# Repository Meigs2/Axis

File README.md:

# Axis

This project is unfinished and is under active development.

For updates, come join the discord: https://discord.gg/SSdEUZB4Xh

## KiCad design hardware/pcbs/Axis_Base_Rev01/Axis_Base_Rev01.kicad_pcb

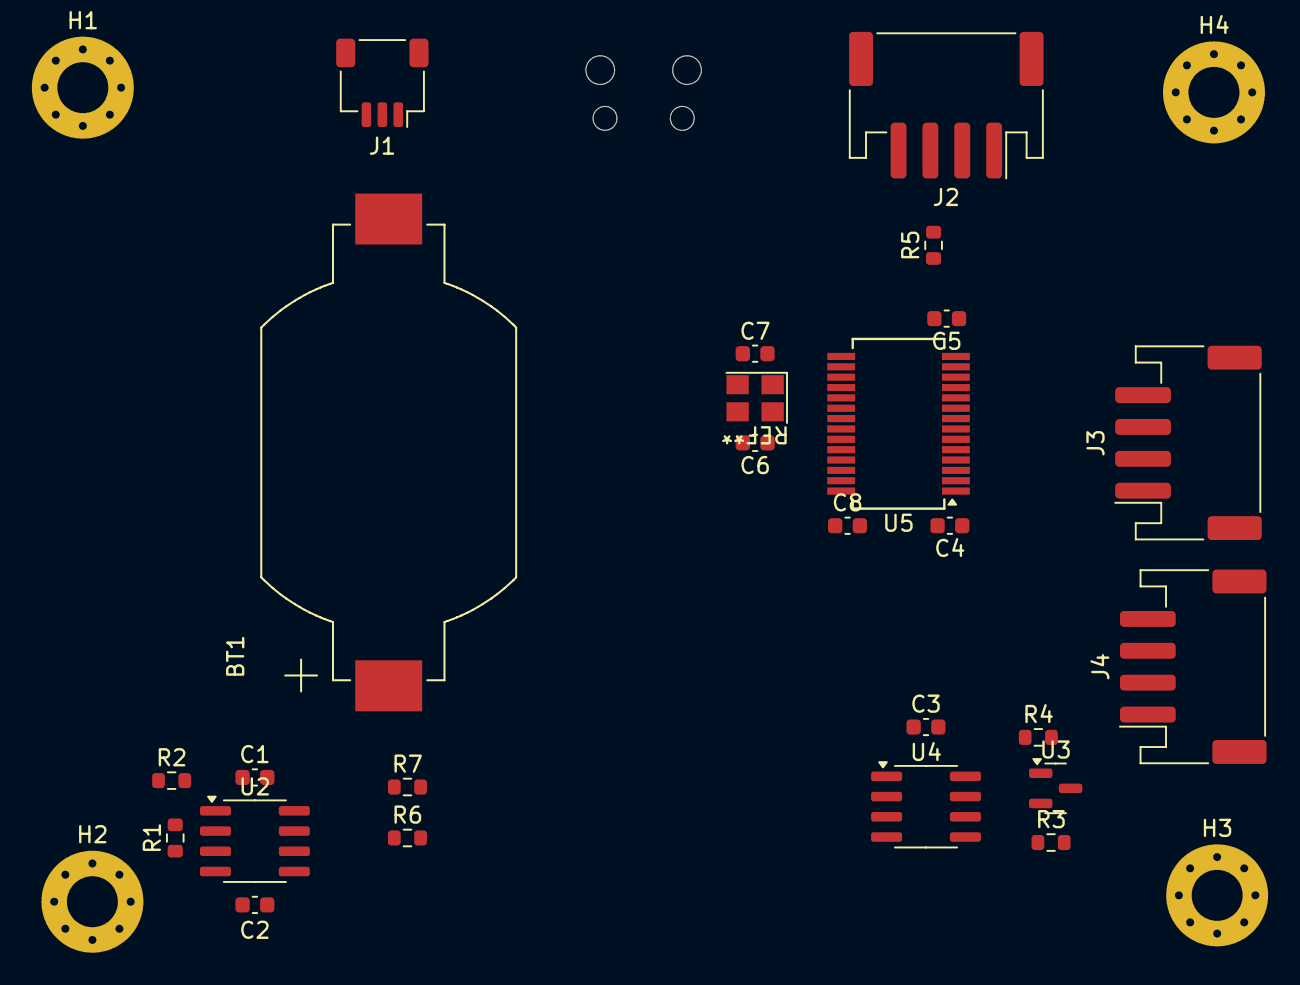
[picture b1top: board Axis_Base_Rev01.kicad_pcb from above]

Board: 4 copper layers, 30 parts (1 on the bottom side), 28 nets, no tracks yet.

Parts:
BT1: BA2032; BAT_BU2032SM-BT-GTR
C1, C2, C3, C4, C5, C8: 0.1u; C_0603_1608Metric
C6, C7: 26p; C_0603_1608Metric
H1, H2, H3, H4: MountingHole; MountingHole_3.2mm_M3_Pad_Via
J1: SWD; JST_SH_SM03B-SRSS-TB_1x03-1MP_P1.00mm_Horizontal
J2: CAN_1; JST_PH_S4B-PH-SM4-TB_1x04-1MP_P2.00mm_Horizontal
J3: CAN_2; JST_PH_S4B-PH-SM4-TB_1x04-1MP_P2.00mm_Horizontal
J4: CAN_3; JST_PH_S4B-PH-SM4-TB_1x04-1MP_P2.00mm_Horizontal
R1, R2, R3, R4, R5, R6, R7: 1k; R_0603_1608Metric
U1: Pico; RPi_Pico_SMD_No_Silkscreen
U2: DS3231MZ; SOIC-8_3.9x4.9mm_P1.27mm
U3: DS2411R; SOT-23
U4: FM24CL16B; SOIC-8_3.9x4.9mm_P1.27mm
U5: MCP251863T-H; SSOP-28_5.3x10.2mm_P0.65mm
Y1: ABM8G-20.000MHZ-18-D2Y-T; Oscillator_Crystal_Abracon_SMD_ABM8G

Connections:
+3V3: C1.1, C3.1, C4.1, C5.1, R1.1, R2.1, R3.1, R6.1, R7.1, U1.36 (3V3_OUT), U2.2 (VCC), U3.2 (VIN), U4.8 (VDD), U5.1 (VIO), U5.14 (VDD)
+5V: C8.1, J2.1, J3.1, J4.1, U1.40 (VBUS), U5.25 (VCC)
+BATT: BT1.1 (+), C2.1, U2.6 (VBAT)
/1WIRE: R4.2, U1.26 (GPIO20)
/CANH: J2.2, J3.2, J4.2, R5.1, U5.4 (CANH)
/CANL: J2.3, J3.3, J4.3, R5.2, U5.3 (CANL)
/I2C0_SCL: R7.2, U1.22 (GPIO17), U2.8 (SCL), U4.6 (SCL)
/I2C0_SDA: R6.2, U1.21 (GPIO16), U2.7 (SDA), U4.5 (SDA)
/RTC_CLK: R1.2, U1.24 (GPIO18), U2.1 (32KHZ)
/SPI0_MISO: U1.1 (GPIO0), U5.11 (SDO)
/SPI0_MOSI: U1.5 (GPIO3), U5.10 (SDI)
/SPI0_SCK: U1.4 (GPIO2), U5.9 (SCK)
/STBY: U1.10 (GPIO7), U5.5 (STBY)
/SWCLK: J1.1, U1.41 (SWCLK)
/SWDIO: J1.3, U1.43 (SWDIO)
/~SPI0_CS: U1.2 (GPIO1), U5.13 (~CS)
/~TIMER_INT: R2.2, U1.25 (GPIO19), U2.3 (~INT/SQW)
/~nINT1: U1.7 (GPIO5), U5.6 (~nINT1)
/~nINT2: U1.9 (GPIO6), U5.7 (~nINT2)
/~nINT: U1.6 (GPIO4), U5.19 (~nINT)
GND: BT1.2 (-), C1.2, C2.2, C3.2, C4.2, C5.2, C8.2, J1.2, J2.4, J3.4, J4.4, U1.3 (GND), U1.8 (GND), U1.13 (GND), U1.18 (GND), U1.23 (GND), U1.28 (GND), U1.38 (GND), U1.42 (GND), U2.5 (GND), U3.3 (GND), U4.4 (VSS), U4.7 (WP), U5.22 (VSS), U5.24 (GND), Y1.1, Y1.3
unnamed: C6.2, Y1.4
unnamed: C7.2, Y1.2
unnamed: R3.2, R4.1, U3.1 (I/O)
unnamed: C7.1, U5.21 (OSC1)
unnamed: C6.1, U5.20 (OSC2)
unnamed: U5.16 (RxCAN), U5.28 (RXD)
unnamed: U5.15 (TxCAN), U5.23 (TXD)

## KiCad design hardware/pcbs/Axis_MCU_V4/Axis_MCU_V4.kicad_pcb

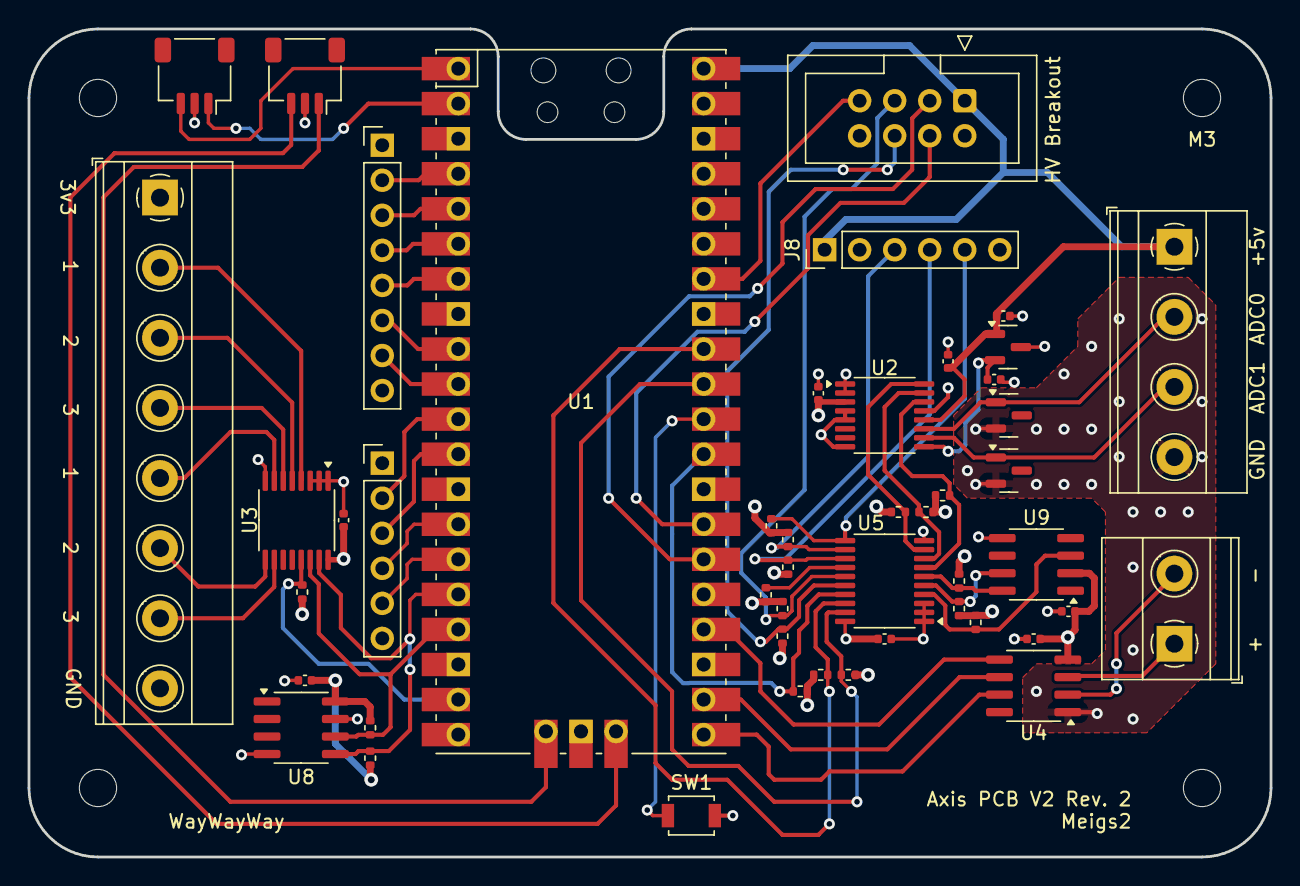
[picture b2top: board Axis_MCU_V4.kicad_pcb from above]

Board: 4 copper layers, 90.0 x 60.0 mm, 51 parts (0 on the bottom side), 53 nets.

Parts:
C1, C2, C3, C4, C5, C7, C8, C9, C10: 0.1u; C_0402_1005Metric
D1, D2: 4.7v; SOT-23
H1, H2, H3, H4: MountingHole; MountingHole_2.7mm_M2.5
J1: SWD; JST_SH_SM03B-SRSS-TB_1x03-1MP_P1.00mm_Horizontal
J2: GPIO; TerminalBlock_Phoenix_MKDS-1,5-8-5.08_1x08_P5.08mm_Horizont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
J3: Conn_01x04; TerminalBlock_Phoenix_MKDS-1,5-4-5.08_1x04_P5.08mm_Horizont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
J4: UART; JST_SH_SM03B-SRSS-TB_1x03-1MP_P1.00mm_Horizontal
J5: Conn_01x02; TerminalBlock_Phoenix_MKDS-1,5-2-5.08_1x02_P5.08mm_Horizont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
J7: EXT_SPI; PinHeader_1x06_P2.54mm_Vertical
J8: EXT_I2C; PinHeader_1x06_P2.54mm_Vertical
J9: GPIO; PinHeader_1x08_P2.54mm_Vertical
J10: HV_IDC; IDC-Header_2x04_P2.54mm_Vertical
R1, R2, R3, R4, R5, R6, R7, R8, R9, R10, R11, R12, R13, R14, R15, R16, R17, R18: 1k; R_0402_1005Metric
SW1: RES; SW_SPST_B3U-1000P
U1: Pico; RPi_Pico_SMD_TH_No_Silkscreen
U2: ADS1119IPWR; TSSOP-16_4.4x5mm_P0.65mm
U3: TCA9534; TSSOP-16_4.4x5mm_P0.65mm
U4: MAX31855EASA; SOIC-8_3.9x4.9mm_P1.27mm
U5: PCA9544APWR; TSSOP-20_4.4x6.5mm_P0.65mm
U7: MAX6107; SOT-23
U8: FM24CL16B; SOIC-8_3.9x4.9mm_P1.27mm
U9: DS3231MZ; SOIC-8_3.9x4.9mm_P1.27mm

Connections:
+3V3: C1.1, C3.1, C4.1, C5.1, C7.1, C10.1, J2.1, J7.1, J8.2, J9.1, J10.2, R1.1, R2.1, R3.1, R4.1, R5.1, R6.1, R7.1, R8.1, R9.1, R10.1, R11.1, R12.1, R13.1, R14.1, R15.1, R16.1, R17.1, R18.1, U1.36 (3V3_OUT), U2.3 (~RESET), U2.13 (DVDD), U3.16 (VDD), U4.4 (V_CC), U5.20 (VDD), U8.8 (VDD), U9.2 (VCC)
+5V: C2.1, C8.1, J3.1, J8.1, J10.1, U1.40 (VBUS), U2.12 (AVDD), U7.1 (IN)
/4.5V_VREF: C9.1, U2.9 (REFP), U7.2 (OUT)
/ADC_0: D1.1 (K), J3.2, U2.11 (AIN0)
/ADC_1: D2.1 (K), J3.3, U2.10 (AIN1)
/ADS_SCL: R8.2, U2.16 (SCL), U5.9 (SC1)
/ADS_SDA: R7.2, U2.15 (SDA), U5.8 (SD1)
/EXT_SCL: J8.4, R17.2, U5.13 (SC2)
/EXT_SDA: J8.3, R16.2, U5.12 (SD2)
/GPIO2: J9.2, U1.4 (GPIO2)
/GPIO3: J9.3, U1.5 (GPIO3)
/GPIO4: J9.4, U1.6 (GPIO4)
/GPIO5: J9.5, U1.7 (GPIO5)
/GPIO6: J9.6, U1.9 (GPIO6)
/GPIO7: J9.7, U1.10 (GPIO7)
/HV_IO1: J10.3, U1.26 (GPIO20)
/HV_IO2: J10.7, U1.34 (GPIO28_ADC2)
/HV_SCL: J10.6, R14.2, U5.16 (SC3)
/HV_SDA: J10.5, R13.2, U5.15 (SD3)
/I2C0_SCL: R2.2, U1.17 (GPIO13), U3.14 (SCL), U8.6 (SCL)
/I2C0_SDA: R1.2, U1.16 (GPIO12), U3.15 (SDA), U8.5 (SDA)
/I2C1_SCL: R4.2, U1.32 (GPIO27_ADC1), U5.18 (SCL)
/I2C1_SDA: R5.2, U1.31 (GPIO26_ADC0), U5.19 (SDA)
/IO_1: J2.2, U3.4 (P0)
/IO_2: J2.3, U3.5 (P1)
/IO_3: J2.4, U3.6 (P2)
/IO_4: J2.5, U3.7 (P3)
/IO_5: J2.6, U3.9 (P4)
/IO_6: J2.7, U3.10 (P5)
/SPI0_RX: U1.21 (GPIO16), U4.7 (SO)
/SPI0_SCK: U1.24 (GPIO18), U4.5 (SCK)
/SPI1_RX: J7.2, U1.11 (GPIO8)
/SPI1_SCK: J7.4, U1.14 (GPIO10)
/SPI1_TX: J7.5, U1.15 (GPIO11)
/SWCLK: J1.1, U1.41 (SWCLK)
/SWDIO: J1.3, U1.43 (SWDIO)
/THCPL1_NEG: J5.2, U4.2 (T-)
/THCPL1_POS: J5.1, U4.3 (T+)
/TIMER_SCL: R11.2, U5.6 (SC0), U9.8 (SCL)
/TIMER_SDA: R10.2, U5.5 (SD0), U9.7 (SDA)
/UART_RX: J4.1, U1.2 (GPIO1)
/UART_TX: J4.3, U1.1 (GPIO0)
/ZC_SIG: J10.4, U1.27 (GPIO21)
/~ADS_RDY: R9.2, U2.14 (~DRDY), U5.7 (~INT1)
/~EXT_INT: J8.5, R18.2, U5.11 (~INT2)
/~INT_3: R15.2, U5.14 (~INT3)
/~IO_INT: R3.2, U1.19 (GPIO14), U3.13 (~INT)
/~MUX_INT: R6.2, U1.29 (GPIO22), U5.17 (~INT)
/~SPI0_CS0: U1.22 (GPIO17), U4.6 (~CS)
/~SPI1_CS0: J7.3, U1.12 (GPIO9)
/~TIMER_INT: R12.2, U5.4 (~INT0), U9.3 (~INT/SQW)
GND: C1.2, C2.2, C3.2, C4.2, C5.2, C7.2, C8.2, C9.2, C10.2, D1.2 (A), D2.2 (A), J1.2, J2.8, J3.4, J4.2, J7.6, J8.6, J9.8, J10.8, SW1.1, U1.3 (GND), U1.8 (GND), U1.13 (GND), U1.18 (GND), U1.23 (GND), U1.28 (GND), U1.38 (GND), U1.42 (GND), U2.1 (A0), U2.2 (A1), U2.4 (DGND), U2.5 (AGND), U2.8 (REFN), U3.1 (A0), U3.2 (A1), U3.3 (A2), U3.8 (GND), U4.1 (GND), U5.1 (A0), U5.2 (A1), U5.3 (A2), U5.10 (VSS), U7.3 (GND), U8.4 (VSS), U8.7 (WP), U9.5 (GND)
unnamed: SW1.2, U1.30 (RUN)

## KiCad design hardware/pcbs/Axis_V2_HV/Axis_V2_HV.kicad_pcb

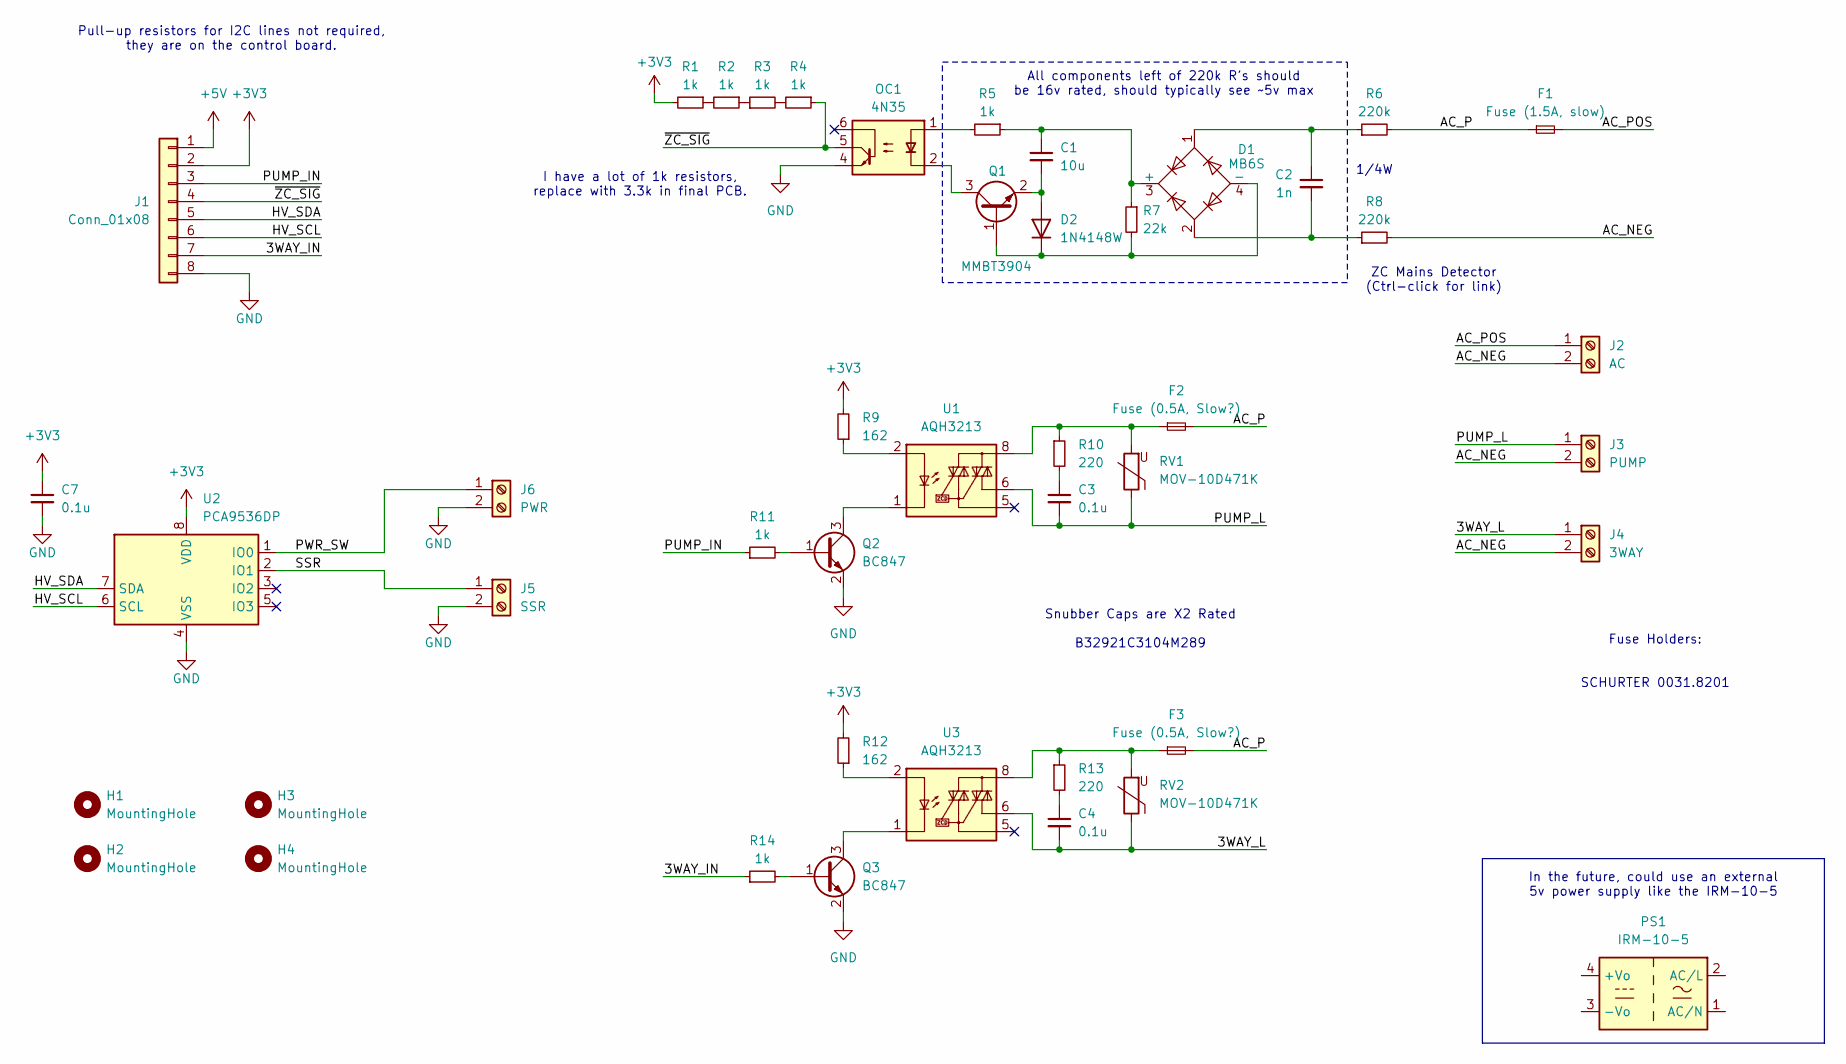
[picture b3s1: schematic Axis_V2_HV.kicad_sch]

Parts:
C1: 10u; C_1206_3216Metric
C2: 1n; C_1206_3216Metric
C3, C4: 0.1u; C_Rect_L13.0mm_W6.0mm_P10.00mm_FKS3_FKP3_MKS4
C7: 0.1u; C_0402_1005Metric
D1: MB6S; TO-269AA
D2: 1N4148W; D_SOD-123
F1: Fuse (1.5A, slow); Fuseholder_Cylinder-5x20mm_Schurter_0031_8201_Horizontal_Op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
F2, F3: Fuse (0.5A, Slow?); Fuseholder_Cylinder-5x20mm_Schurter_0031_8201_Horizontal_Op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
H1, H2, H3, H4: MountingHole; MountingHole_2.7mm_M2.5
J1: Conn_01x08; IDC-Header_2x04_P2.54mm_Vertical
J2: AC; TerminalBlock_Phoenix_MKDS-1,5-2-5.08_1x02_P5.08mm_Horizont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
J3: PUMP; TerminalBlock_Phoenix_MKDS-1,5-2-5.08_1x02_P5.08mm_Horizont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
J4: 3WAY; TerminalBlock_Phoenix_MKDS-1,5-2-5.08_1x02_P5.08mm_Horizont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
J5: SSR; TerminalBlock_Phoenix_MKDS-1,5-2-5.08_1x02_P5.08mm_Horizont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
J6: PWR; TerminalBlock_Phoenix_MKDS-1,5-2-5.08_1x02_P5.08mm_Horizont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
OC1: 4N35; SMDIP-6_W7.62mm
PS1: IRM-10-5; Converter_ACDC_MeanWell_IRM-10-xx_THT
Q1: MMBT3904; SOT-23
Q2, Q3: BC847; SOT-23
R1, R2, R3, R4, R11, R14: 1k; R_0402_1005Metric
R5: 1k; R_1206_3216Metric
R6, R8: 220k; R_Axial_DIN0207_L6.3mm_D2.5mm_P10.16mm_Horizontal
R7: 22k; R_1206_3216Metric
R9, R12: 162; R_0603_1608Metric
R10, R13: 220; R_Axial_DIN0207_L6.3mm_D2.5mm_P10.16mm_Horizontal
RV1, RV2: MOV-10D471K; RV_Disc_D12mm_W7.5mm_P7.5mm
U1, U3: AQH3213; DIP-8-N7_W7.62mm
U2: PCA9536DP; TSSOP-8_3x3mm_P0.65mm

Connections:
+3V3: C7.1, J1.2, R1.2, R9.2, R12.2, U2.8 (VDD)
+5V: J1.1
/3WAY_IN: J1.7, R14.1
/3WAY_L: C4.2, J4.1, RV2.1, U3.6
/AC_NEG: J2.2, J3.2, J4.2, R8.2
/AC_P: F1.1, F2.2, F3.2, R6.2
/AC_POS: F1.2, J2.1
/HV_SCL: J1.6, U2.6 (SCL)
/HV_SDA: J1.5, U2.7 (SDA)
/PUMP_IN: J1.3, R11.1
/PUMP_L: C3.2, J3.1, RV1.1, U1.6
/PWR_SW: J6.1, U2.1 (IO0)
/SSR: J5.1, U2.2 (IO1)
/~ZC_SIG: J1.4, OC1.5, R4.1
GND: C7.2, J1.8, J5.2, J6.2, OC1.4, Q2.2 (E), Q3.2 (E), U2.4 (VSS)
unnamed: C2.1, D1.1, R6.1
unnamed: C2.2, D1.2, R8.1
unnamed: C3.1, R10.2
unnamed: C4.1, R13.2
unnamed: C1.1, D1.3 (+), R5.1, R7.1
unnamed: D1.4 (-), D2.1 (K), Q1.1 (B), R7.2
unnamed: C1.2, D2.2 (A), Q1.2 (E)
unnamed: F2.1, R10.1, RV1.2, U1.8
unnamed: F3.1, R13.1, RV2.2, U3.8
unnamed: OC1.1, R5.2
unnamed: OC1.2, Q1.3 (C)
unnamed: Q2.1 (B), R11.2
unnamed: Q2.3 (C), U1.1, U1.3, U1.4
unnamed: Q3.1 (B), R14.2
unnamed: Q3.3 (C), U3.1, U3.3, U3.4
unnamed: R1.1, R2.2
unnamed: R2.1, R3.1
unnamed: R3.2, R4.2
unnamed: R9.1, U1.2
unnamed: R12.1, U3.2

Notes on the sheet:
Pull-up resistors for I2C lines not required, they are on the control board.
I have a lot of 1k resistors, replace with 3.3k in final PCB.
ZC Mains Detector (Ctrl-click for link)
1/4W
In the future, could use an external 5v power supply like the IRM-10-5
All components left of 220k R's should be 16v rated, should typically see ~5v max
Fuse Holders: SCHURTER 0031.8201
Snubber Caps are X2 Rated B32921C3104M289

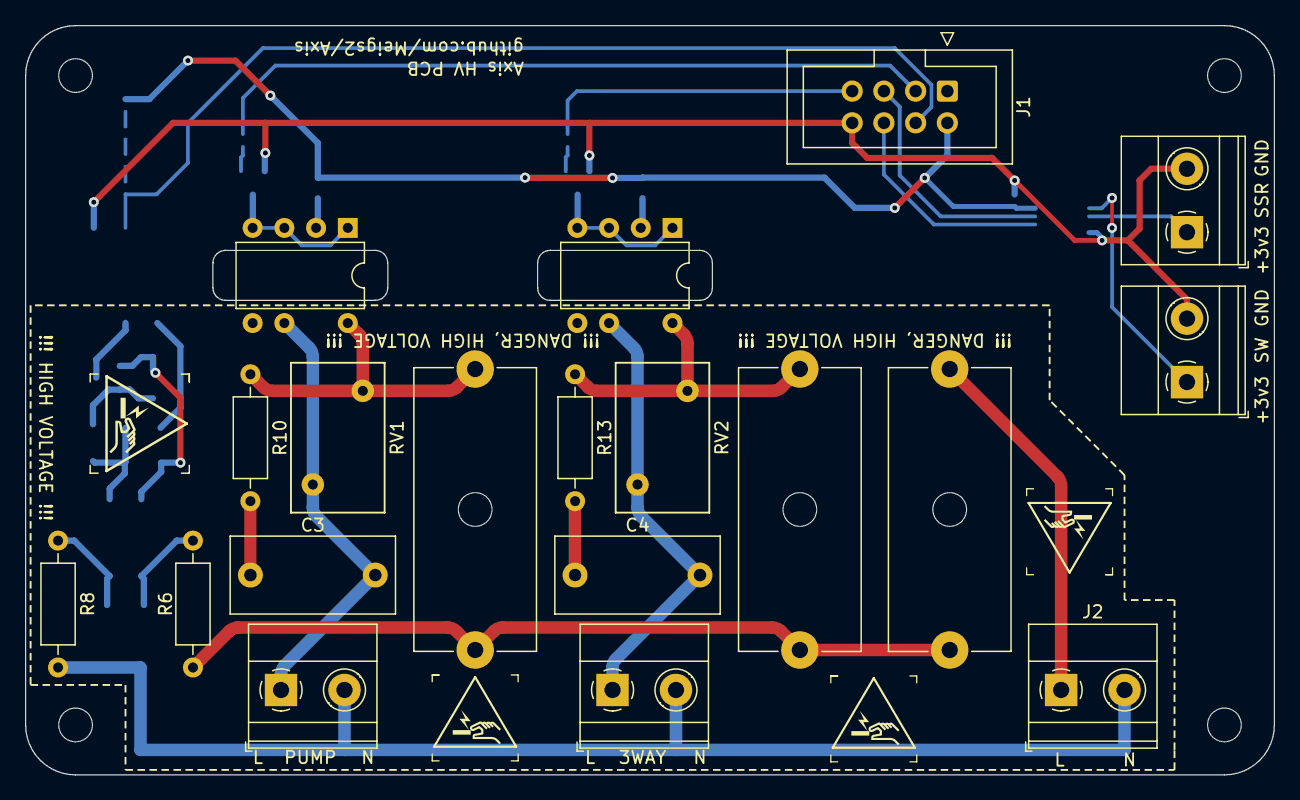
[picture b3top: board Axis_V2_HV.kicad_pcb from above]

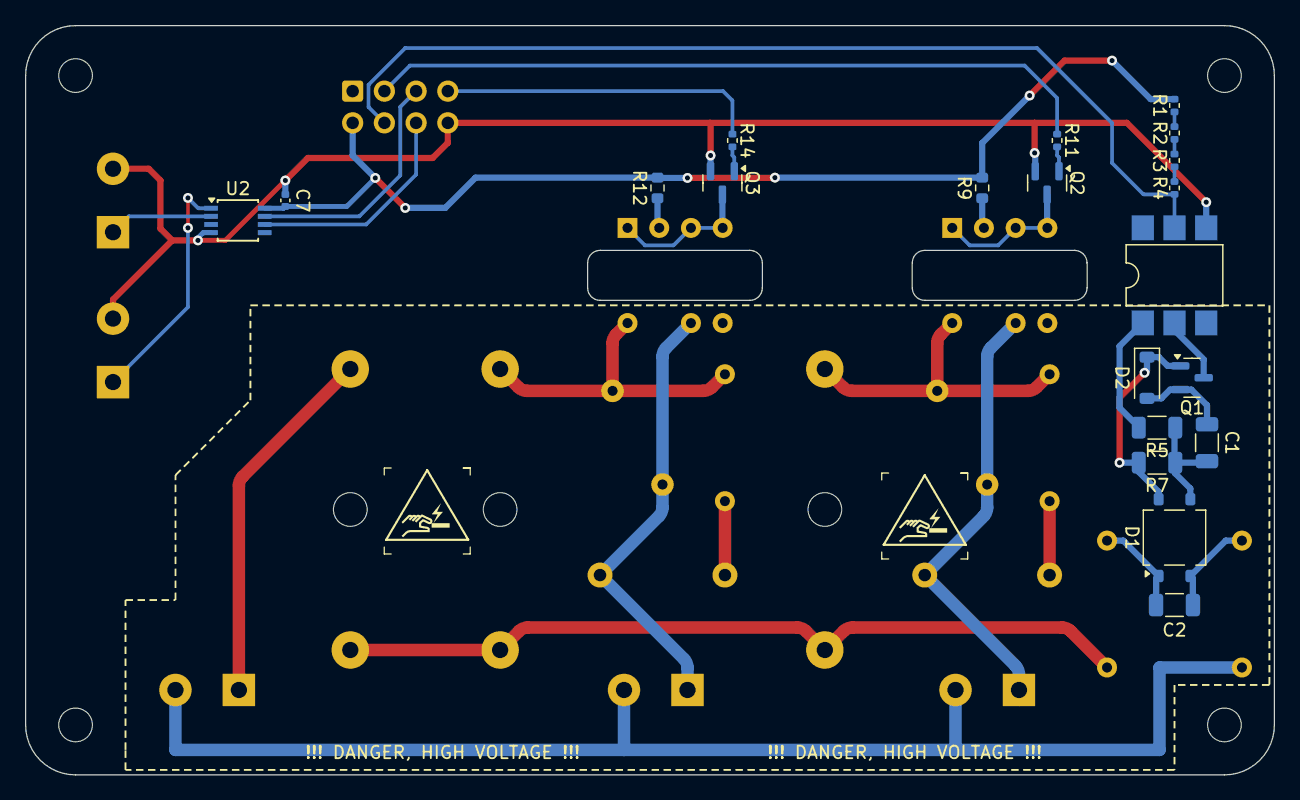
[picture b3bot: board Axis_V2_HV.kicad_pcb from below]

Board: 2 copper layers, 100.0 x 60.0 mm, 43 parts (20 on the bottom side), 34 nets.

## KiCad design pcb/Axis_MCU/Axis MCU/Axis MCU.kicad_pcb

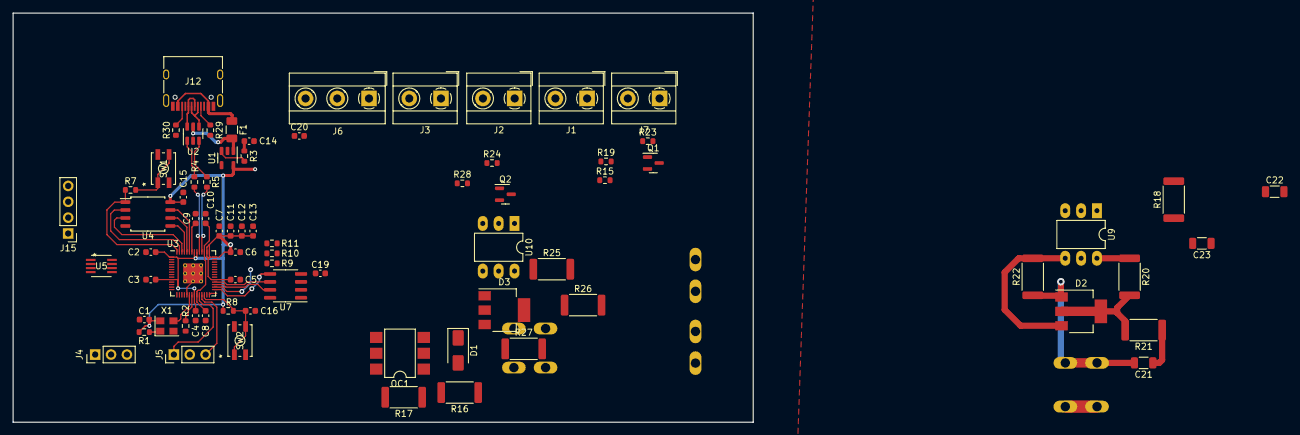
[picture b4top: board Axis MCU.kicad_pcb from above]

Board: 2 copper layers, 118.5 x 65.5 mm, 80 parts (0 on the bottom side), 65 nets.

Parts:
C1, C10, C11, C14: 1uF; C_0603_1608Metric
C2, C3, C4, C5, C6, C7, C8, C9, C13: 100nF; C_0603_1608Metric
C12: 10uF; C_0603_1608Metric
C15: 100nf; C_0603_1608Metric
C16: 1uf; C_0603_1608Metric
C19: 0.1u; C_0603_1608Metric
C20: 1u; C_0603_1608Metric
C21, C22, C23: 10nf; C_1206_3216Metric
D1: BYG23M-E3/TR; D_SMA
D2, D3: Z0107MN; SOT-223
F1: 500mA; Fuse_1206_3216Metric
J1: BREW_SW; TerminalBlock_MetzConnect_Type101_RT01602HBWC_1x02_P5.08mm_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
J2: STEAM_SW; TerminalBlock_MetzConnect_Type101_RT01602HBWC_1x02_P5.08mm_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
J3: BOILER_SSR; TerminalBlock_MetzConnect_Type101_RT01602HBWC_1x02_P5.08mm_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
J4: UART; PinHeader_1x03_P2.54mm_Vertical
J5: DEBUG; PinHeader_1x03_P2.54mm_Vertical
J6: PRES_SENS; TerminalBlock_MetzConnect_Type101_RT01603HBWC_1x03_P5.08mm_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
J7: THCPL; TerminalBlock_MetzConnect_Type101_RT01602HBWC_1x02_P5.08mm_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
J8: AC_L; Quick Disconnect
J9: AC_N; Quick Disconnect
J10: PUMP_L; Quick Disconnect
J11: 3WAY_L; Quick Disconnect
J12: USB_C_Receptacle_USB2.0; USB_C_Receptacle_HRO_TYPE-C-31-M-12
J13: 3WAY_N; Quick Disconnect
J14: PUMP_N; Quick Disconnect
J15: SCREEN; PinHeader_1x04_P2.54mm_Vertical
OC1: 4N35; SMDIP-6_W7.62mm
Q1, Q2: BC847; SOT-23
R1, R8: 10K; R_0603_1608Metric
R2: 1k; R_0603_1608Metric
R3, R4, R5: 27R; R_0603_1608Metric
R7: 1K; R_0603_1608Metric
R9, R10, R11: 660; R_0603_1608Metric
R15: 4.7k; R_0603_1608Metric
R16, R17: 100k; R_2512_6332Metric
R18, R21, R26: 39; R_2512_6332Metric
R19, R24: 360; R_0603_1608Metric
R20, R22, R25, R27: 360; R_2512_6332Metric
R23, R28: 27k; R_0603_1608Metric
R29, R30: 5k1; R_0603_1608Metric
SW1: BOOT; SWITCH_EVQP2_PAN
SW2: RESET; SWITCH_EVQP2_PAN
U1: AP2112K-3.3; SOT-23-5
U2: USBLC6-2SC6; SOT-23-6
U3: RP2040; RP2040-QFN-56
U4: W25Q128JVS; SOIC-8_5.23x5.23mm_P1.27mm
U5: 74LVC3G14; DCT8
U7: MAX31855; SOIC-8_3.9x4.9mm_P1.27mm
U9, U10: MOC3063M; DIP-6_W7.62mm_LongPads
X1: ASE-12.0MHz; Oscillator_SMD_Abracon_ASE-4Pin_3.2x2.5mm

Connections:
+1V1: C8.1, C9.1, C10.1, U3.23 (DVDD), U3.45 (VREG_VOUT), U3.50 (DVDD)
+3V3: C1.1, C2.1, C3.1, C4.1, C5.1, C6.1, C7.1, C11.1, C12.1, C13.1, C15.1, C19.1, C20.2, J1.2, J2.2, J6.3, J15.2, R1.1, R8.1, R15.2, R19.2, R24.1, U1.5 (VOUT), U3.1 (IOVDD), U3.10 (IOVDD), U3.22 (IOVDD), U3.33 (IOVDD), U3.42 (IOVDD), U3.43 (ADC_AVDD), U3.44 (VREG_IN), U3.48 (USB_VDD), U3.49 (IOVDD), U4.8 (VCC), U7.4 (V_CC), X1.4 (Vdd)
+5V: C14.2, F1.2, R3.1, U1.1 (VIN), U2.5 (VBUS)
/3WAY_OUT: R28.2, U3.18 (GPIO15)
/BOIL_OUT: R11.2, U3.37 (GPIO25)
/BREW_SW: R9.1, U3.34 (GPIO22)
/CC1: J12.A5 (CC1), R29.1
/CC2: J12.B5 (CC2), R30.1
/High Voltage/AC_L: D2.2 (A2), D2.4 (A4), D3.2 (A2), D3.4 (A4), J8.1, R17.2, R18.2, R20.2, R21.2, R25.2, R26.2
/High Voltage/AC_N: C23.2, D1.2 (A), J9.1, J13.1, J14.1, OC1.2
/MAX_CS: U3.32 (GPIO21), U7.6 (~CS)
/MAX_MISO: U3.31 (GPIO20), U7.7 (SO)
/MAX_SCK: U3.29 (GPIO18), U7.5 (SCK)
/PRES_SENS: J6.1, U3.41 (GPIO29_ADC3)
/PUMP_OUT: R23.2, U3.17 (GPIO14)
/Peripherals/NEG_THCPL: J7.1, U7.2 (T-)
/Peripherals/POS_THCPL: J7.2, U7.3 (T+)
/QSPI_SCLK: U3.52 (QSPI_SCLK), U4.6 (CLK)
/QSPI_SD0: U3.53 (QSPI_SD0), U4.5 (DI(IO0))
/QSPI_SD1: U3.55 (QSPI_SD1), U4.2 (DO(IO1))
/QSPI_SD2: U3.54 (QSPI_SD2), U4.3 (IO2)
/QSPI_SD3: U3.51 (QSPI_SD3), U4.7 (IO3)
/QSPI_SS: R7.1, U3.56 (QSPI_SS), U4.1 (~CS)
/SCREEN_SCL: J15.3, U3.9 (GPIO7)
/SCREEN_SDA: J15.4, U3.8 (GPIO6)
/STEAM_SW: R10.2, U3.35 (GPIO23)
/SWCLK: J5.1, U3.24 (SWCLK)
/SWDIO: J5.3, U3.25 (SWD)
/UART_RX: J4.1, U3.16 (GPIO13)
/UART_TX: J4.3, U3.15 (GPIO12)
/USB_D+: R4.2, U3.47 (USB_DP)
/USB_D-: R5.2, U3.46 (USB_DM)
/XIN: U3.20 (XIN), X1.3 (OUT)
/XOUT: R2.1, U3.21 (XOUT)
/~RESET: C16.2, R8.2, SW2.1, SW2.3, U3.26 (RUN)
/~USB_BOOT: R7.2, SW1.1, SW1.3
/~ZC_SIG: OC1.5, R15.1, U3.28 (GPIO17)
D_N: R5.1, U2.3 (I/O2)
D_P: R4.1, U2.1 (I/O1)
D_USB_N: J12.A7 (D-), J12.B7 (D-), U2.4 (I/O2)
D_USB_P: J12.A6 (D+), J12.B6 (D+), U2.6 (I/O1)
GND: C1.2, C2.2, C3.2, C4.2, C5.2, C6.2, C7.2, C8.2, C9.2, C10.2, C11.2, C12.2, C13.2, C14.1, C15.2, C16.1, C19.2, C20.1, J3.1, J4.2, J5.2, J6.2, J12.A1 (GND), J12.A12 (GND), J12.B1 (GND), J12.B12 (GND), J12.S1 (SHIELD), J15.1, OC1.4, Q1.2 (E), Q2.2 (E), R2.2, R29.2, R30.2, SW1.2, SW1.4, SW2.2, SW2.4, U1.2 (GND), U2.2 (GND), U3.19 (TESTEN), U3.57 (GND), U4.4 (GND), U7.1 (GND), X1.2 (GND)
unnamed: C21.1, R21.1
unnamed: C22.1, R26.1
unnamed: C23.1, R18.1
unnamed: D1.1 (K), OC1.1, R16.1
unnamed: C21.2, D2.1 (A1), J10.1, R22.1
unnamed: D2.3 (G), R22.2, U9.4
unnamed: C22.2, D3.1 (A1), J11.1, R27.1
unnamed: D3.3 (G), R27.2, U10.4
unnamed: J1.1, R9.2
unnamed: J2.1, R10.1
unnamed: J3.2, R11.1
unnamed: Q1.1 (B), R23.1
unnamed: Q1.3 (C), U9.2
unnamed: Q2.1 (B), R28.1
unnamed: Q2.3 (C), U10.2
unnamed: R16.2, R17.1
unnamed: R19.1, U9.1
unnamed: R20.1, U9.6
unnamed: R24.2, U10.1
unnamed: R25.1, U10.6
unnamed: R3.2, U1.3 (EN)
unnamed: R1.2, X1.1 (EN)
VBUS: F1.1, J12.A4 (VBUS), J12.A9 (VBUS), J12.B4 (VBUS), J12.B9 (VBUS)

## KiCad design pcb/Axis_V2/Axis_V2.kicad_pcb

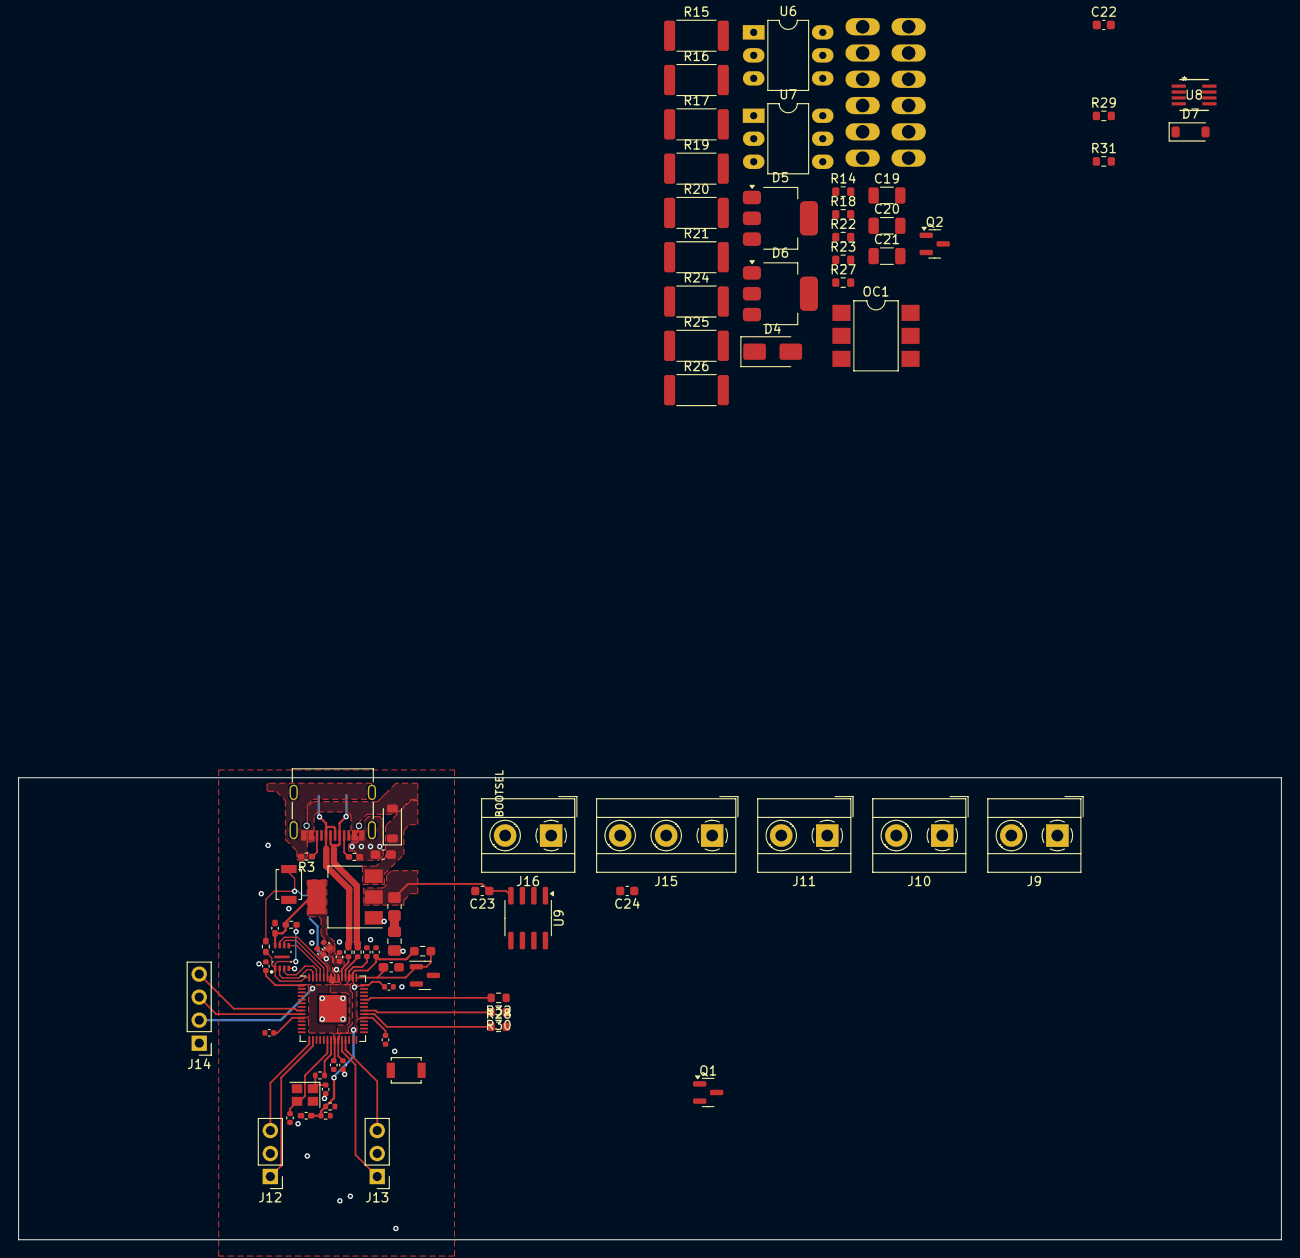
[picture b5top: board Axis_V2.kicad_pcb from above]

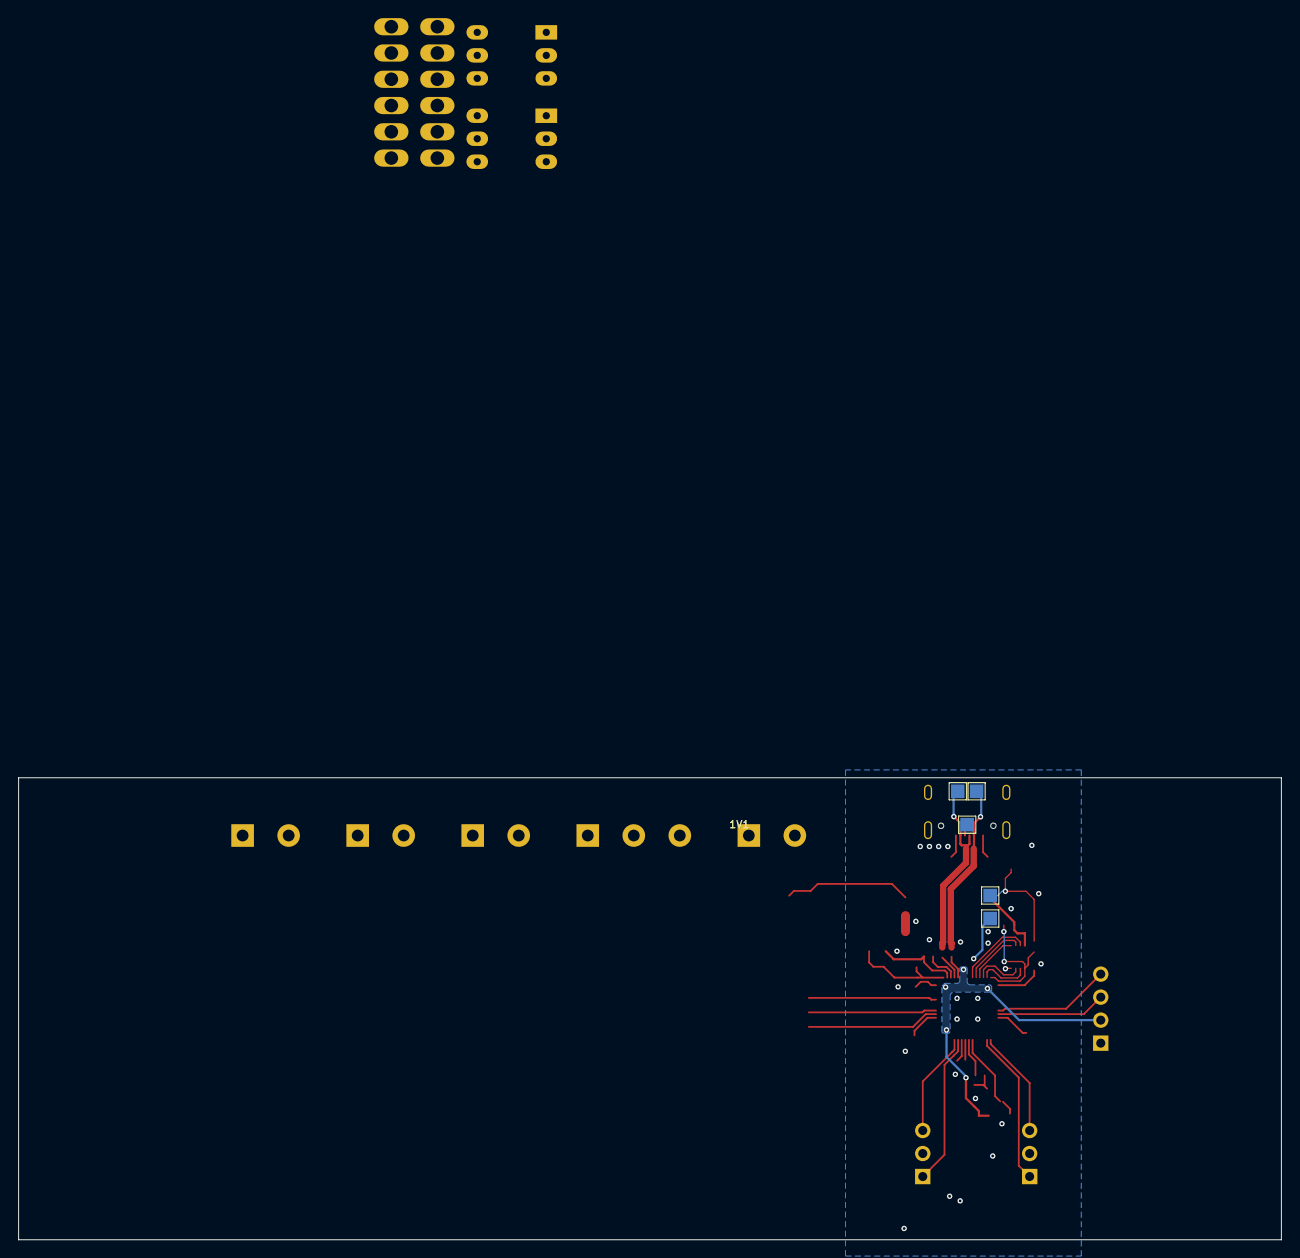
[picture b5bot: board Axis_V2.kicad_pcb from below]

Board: 2 copper layers, 139.4 x 51.0 mm, 93 parts (5 on the bottom side), 66 nets.

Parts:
C1, C5: 100n; C_0402_1005Metric_Pad0.74x0.62mm_HandSolder
C2, C3: 18p; C_0402_1005Metric
C4: 2.2u; C_0603_1608Metric_Pad1.08x0.95mm_HandSolder
C6: 10u; C_0805_2012Metric_Pad1.18x1.45mm_HandSolder
C7: 10n C0G; C_0603_1608Metric_Pad1.08x0.95mm_HandSolder
C8, C9, C11, C13, C14, C15, C16, C17, C18: 100n; C_0402_1005Metric
C10, C12: 1u; C_0402_1005Metric
C19, C20, C21: 10nf; C_1206_3216Metric
C22: 1uF; C_0603_1608Metric
C23: 0.1u; C_0603_1608Metric
C24: 1u; C_0603_1608Metric
D1: B5819W; D_SOD-123
D4: BYG23M-E3/TR; D_SMA
D5, D6: Z0107MN; SOT-223
D7: 1N4148W; D_SOD-123
J1: USB_C_Receptacle_USB2.0; USB_C_Receptacle_Palconn_UTC16-G
J3: AC_L; Quick Disconnect
J4: AC_N; Quick Disconnect
J5: PUMP_L; Quick Disconnect
J6: PUMP_N; Quick Disconnect
J7: 3WAY_L; Quick Disconnect
J8: 3WAY_N; Quick Disconnect
J9: BREW_SW; TerminalBlock_MetzConnect_Type101_RT01602HBWC_1x02_P5.08mm_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
J10: STEAM_SW; TerminalBlock_MetzConnect_Type101_RT01602HBWC_1x02_P5.08mm_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
J11: BOILER_SSR; TerminalBlock_MetzConnect_Type101_RT01602HBWC_1x02_P5.08mm_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
J12: UART; PinHeader_1x03_P2.54mm_Vertical
J13: DEBUG; PinHeader_1x03_P2.54mm_Vertical
J14: SCREEN; PinHeader_1x04_P2.54mm_Vertical
J15: PRES_SENS; TerminalBlock_MetzConnect_Type101_RT01603HBWC_1x03_P5.08mm_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
J16: THCPL; TerminalBlock_MetzConnect_Type101_RT01602HBWC_1x02_P5.08mm_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
OC1: 4N35; SMDIP-6_W7.62mm
Q1, Q2: BC847; SOT-23
R1: 1k; R_0402_1005Metric_Pad0.72x0.64mm_HandSolder
R2: DNP; R_0402_1005Metric_Pad0.72x0.64mm_HandSolder
R3, R4: 5.1k; R_0402_1005Metric_Pad0.72x0.64mm_HandSolder
R5, R10, R11: 1k; R_0402_1005Metric
R6: 470mOhm; R_0805_2012Metric_Pad1.20x1.40mm_HandSolder
R7: 150; R_0603_1608Metric_Pad0.98x0.95mm_HandSolder
R8, R9: 27; R_0402_1005Metric
R14: 4.7k; R_0603_1608Metric
R15, R16: 100k; R_2512_6332Metric
R17, R20, R25: 39; R_2512_6332Metric
R18, R23: 360; R_0603_1608Metric
R19, R21, R24, R26: 360; R_2512_6332Metric
R22, R27: 27k; R_0603_1608Metric
R28, R30, R32: 660; R_0603_1608Metric
R29: 51k; R_0603_1608Metric
R31: 22k; R_0603_1608Metric
SW1: BOOTSEL; SW_SPST_B3U-1000P
SW2: RES; SW_SPST_B3U-1000P
TP1: BOOTSEL; TestPoint_Pad_1.5x1.5mm
TP2: VREG; TestPoint_Pad_1.5x1.5mm
TP4: GND; TestPoint_Pad_1.5x1.5mm
TP5: D+; TestPoint_Pad_1.5x1.5mm
TP7: D-; TestPoint_Pad_1.5x1.5mm
U2: W25Q16JVUXIQ; IC_W25Q16JVUXIQ_TR
U3: AMS1117-3.3; SOT-223-3_TabPin2
U4: LM4040DBZ-3; SOT-23
U5: RP2040; RP2040-QFN-56
U6, U7: MOC3063M; DIP-6_W7.62mm_LongPads
U8: SN74LVC3G14DCTR; DCT8
U9: MAX31855; SOIC-8_3.9x4.9mm_P1.27mm
Y1: ECS-120-12-36-AGN-TR3; Crystal_SMD_2520-4Pin_2.5x2.0mm

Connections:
+1V1: C8.1, C9.1, C10.1, TP2.1, U5.23 (DVDD), U5.45 (VREG_VOUT), U5.50 (DVDD)
+3V3: C1.1, C5.1, C11.1, C12.1, C13.1, C14.1, C15.1, C16.1, C17.1, C18.1, C23.1, C24.2, J9.2, J10.2, J14.2, J15.3, R2.1, R6.2, R7.2, R10.1, R11.1, R14.2, R18.2, R23.1, R29.1, U2.8 (VCC), U3.2 (VO), U5.1 (IOVDD), U5.10 (IOVDD), U5.22 (IOVDD), U5.33 (IOVDD), U5.42 (IOVDD), U5.44 (VREG_IN), U5.48 (USB_VDD), U5.49 (IOVDD), U8.8 (VCC), U9.4 (V_CC)
+5V: C4.1, D1.1 (K), U3.3 (VI)
/3V0_VREF: C7.1, R7.1, U4.1 (K), U5.43 (ADC_AVDD)
/3WAY_OUT: R27.2, U5.18 (GPIO15)
/BOIL_OUT: R32.2, U5.38 (GPIO26_ADC0)
/BREW_SW: R28.1, U5.34 (GPIO22)
/D+: J1.A6 (D+), J1.B6 (D+), R8.1, TP5.1
/D-: J1.A7 (D-), J1.B7 (D-), R9.1, TP7.1
/DN: R9.2, U5.46 (USB_DM)
/DP: R8.2, U5.47 (USB_DP)
/High Voltage/AC_L: D5.2 (A2), D5.4 (A4), D6.2 (A2), D6.4 (A4), J3.1, R16.2, R17.2, R19.2, R20.2, R24.2, R25.2
/High Voltage/AC_N: C19.2, D4.2 (A), J4.1, J6.1, J8.1, OC1.2
/MAX_CS: U5.32 (GPIO21), U9.6 (~CS)
/MAX_MISO: U5.31 (GPIO20), U9.7 (SO)
/MAX_SCK: U5.29 (GPIO18), U9.5 (SCK)
/PRES_SENS: J15.1, U5.41 (GPIO29_ADC3)
/PUMP_OUT: R22.2, U5.17 (GPIO14)
/Peripherals/NEG_THCPL: J16.1, U9.2 (T-)
/Peripherals/POS_THCPL: J16.2, U9.3 (T+)
/QSPI_SCLK: U2.6 (CLK), U5.52 (QSPI_SCLK)
/QSPI_SD0: U2.5 (DI(IO0)), U5.53 (QSPI_SD0)
/QSPI_SD1: U2.2 (DO(IO1)), U5.55 (QSPI_SD1)
/QSPI_SD2: U2.3 (IO2), U5.54 (QSPI_SD2)
/QSPI_SD3: U2.7 (IO3), U5.51 (QSPI_SD3)
/QSPI_SS: R1.1, R2.2, U2.1 (~CS), U5.56 (QSPI_SS)
/RUN: SW2.1, U5.26 (RUN)
/SCREEN_SCL: J14.3, U5.9 (GPIO7)
/SCREEN_SDA: J14.4, U5.8 (GPIO6)
/STEAM_SW: R30.2, U5.35 (GPIO23)
/SWCLK: J13.1, U5.24 (SWCLK)
/SWDIO: J13.3, U5.25 (SWD)
/UART_RX: J12.1, U5.16 (GPIO13)
/UART_TX: J12.3, U5.15 (GPIO12)
/XIN: C2.1, U5.20 (XIN), Y1.3
/XOUT: R5.1, U5.21 (XOUT)
/~ZC_SIG: OC1.5, R14.1, U5.28 (GPIO17)
GND: C1.2, C2.2, C3.2, C4.2, C5.2, C6.2, C7.2, C8.2, C9.2, C10.2, C11.2, C12.2, C13.2, C14.2, C15.2, C16.2, C17.2, C18.2, C22.2, C23.2, C24.1, J1.A1 (GND), J1.A12 (GND), J1.B1 (GND), J1.B12 (GND), J1.S1 (SHIELD), J11.1, J12.2, J13.2, J14.1, J15.2, OC1.4, Q1.2 (E), Q2.2 (E), R3.2, R4.2, SW1.1, SW2.2, TP4.1, U2.4 (GND), U3.1 (GND), U4.2 (A), U5.19 (TESTEN), U5.57 (GND), U8.4 (GND), U9.1 (GND), Y1.2, Y1.4
unnamed: C3.1, R5.2, Y1.1
unnamed: C6.1, R6.1
unnamed: C19.1, R17.1
unnamed: C20.1, R20.1
unnamed: C21.1, R25.1
unnamed: D4.1 (K), OC1.1, R15.1
unnamed: C20.2, D5.1 (A1), J5.1, R21.1
unnamed: D5.3 (G), R21.2, U6.4
unnamed: C21.2, D6.1 (A1), J7.1, R26.1
unnamed: D6.3 (G), R26.2, U7.4
unnamed: D7.2 (A), R29.2, R31.2
unnamed: C22.1, D7.1 (K), R31.1, U8.1
unnamed: J1.A5 (CC1), R4.1
unnamed: J1.B5 (CC2), R3.1
unnamed: J9.1, R28.2
unnamed: J10.1, R30.1
unnamed: J11.2, R32.1
unnamed: Q1.1 (B), R22.1
unnamed: Q1.3 (C), U6.2
unnamed: Q2.1 (B), R27.1
unnamed: Q2.3 (C), U7.2
unnamed: R1.2, SW1.2, TP1.1
unnamed: R15.2, R16.1
unnamed: R18.1, U6.1
unnamed: R19.1, U6.6
unnamed: R23.2, U7.1
unnamed: R24.1, U7.6
VBUS: D1.2 (A), J1.A4 (VBUS), J1.A9 (VBUS), J1.B4 (VBUS), J1.B9 (VBUS)
